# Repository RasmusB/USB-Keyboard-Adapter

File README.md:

# USB-Keyboard-Adapter

An ATmega32u4 based keyboard controller. This was designed for use with a Psion Series 5mx keyboard, but should work for other keyboards also.

* PCB contains KiCad files for the device itself
* Firmware/Psion-Keyboard-Firmware contains an Arduino sketch for the firmware
* Firmware/ScanTheMatrix is a sketch for scanning the matrix of a keyboard. This is only meant as a tool to map a keyboard with an unknown pinout.

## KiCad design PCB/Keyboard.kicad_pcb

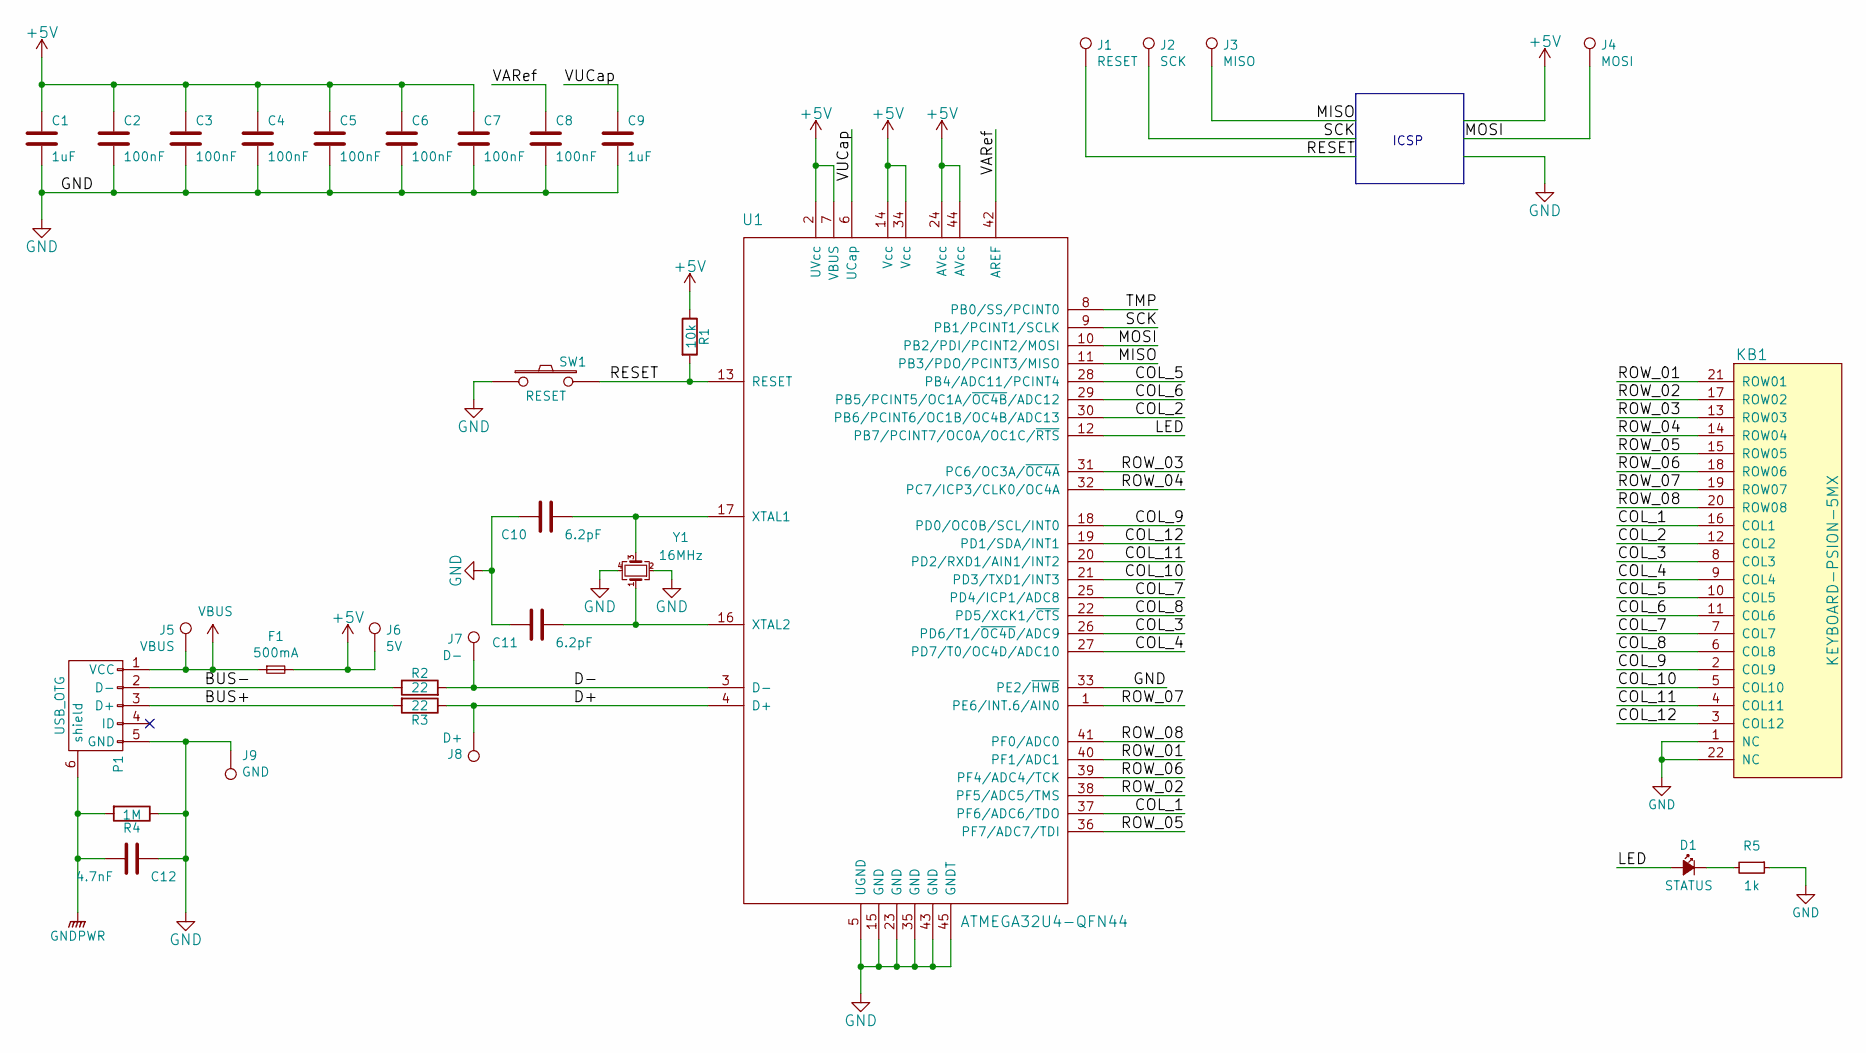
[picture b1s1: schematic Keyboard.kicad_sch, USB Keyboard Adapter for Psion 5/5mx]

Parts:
C1, C9: 1uF; C_0402_1005Metric; MPN CL05A105KA5NQNC; JLCPCB C52923
C2, C3, C4, C5, C6, C7, C8: 100nF; C_0402_1005Metric; MPN CL05B104KO5NNNC; JLCPCB C1525
C10, C11: 6.2pF; C_0402_1005Metric; MPN CC0402CRNPO9BN6R2; JLCPCB C325456
C12: 4.7nF; C_0402_1005Metric; MPN 0402B472K500NT; JLCPCB C1538
D1: STATUS; LED_0402_1005Metric; MPN XL-1005SURC; JLCPCB C965790
F1: 500mA; Fuse_0603_1608Metric; MPN 0603L100SLYR; JLCPCB C207017
J1: RESET; TESTPOINT-1mm-NO_TEXT
J2: SCK; TESTPOINT-1mm-NO_TEXT
J3: MISO; TESTPOINT-1mm-NO_TEXT
J4: MOSI; TESTPOINT-1mm-NO_TEXT
J5: VBUS; TESTPOINT-1mm-NO_TEXT
J6: 5V; TESTPOINT-1mm-NO_TEXT
J7: D-; TESTPOINT-1mm-NO_TEXT
J8: D+; TESTPOINT-1mm-NO_TEXT
J9: GND; TESTPOINT-1mm-NO_TEXT
KB1: KEYBOARD-PSION-5MX; FPC_22p-JUSHUO_AFC01-S22FCC-00; MPN AFC01-S22FCC-00; JLCPCB C262275
P1: USB_OTG; USB_Micro-B_Amphenol_10118194_Horizontal; MPN 10118194-0001LF; JLCPCB C132563
R1: 10k; R_0402_1005Metric; MPN 0402WGF1002TCE; JLCPCB C25744
R2, R3: 22; R_0402_1005Metric; MPN 0402WGF220JTCE; JLCPCB C25092
R4: 1M; R_0402_1005Metric; MPN 0402WGF1004TCE; JLCPCB C26083
R5: 1k; R_0402_1005Metric; MPN 0402WGF1001TCE; JLCPCB C11702
SW1: RESET; ALPS-SKRMAAE010; MPN SKRMAAE010; JLCPCB C115358
U1: ATMEGA32U4-QFN44; QFN-44-1EP_7x7mm_P0.5mm_EP5.2x5.2mm; MPN ATMEGA32U4-MU; JLCPCB C112161
Y1: 16MHz; Crystal_SMD_Abracon_ABM10-4Pin_2.5x2.0mm; MPN ABM10W-16.0000MHZ-8-D1X-T3; JLCPCB C1986789

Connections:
+5V: C1.1, C2.1, C3.1, C4.1, C5.1, C6.1, C7.1, F1.2, J6.1, R1.1, U1.2 (UVcc), U1.7 (VBUS), U1.14 (Vcc), U1.24 (AVcc), U1.34 (Vcc), U1.44 (AVcc)
/BUS+: P1.3 (D+), R3.2
/BUS-: P1.2 (D-), R2.1
/COL_1: KB1.16 (COL1), U1.37 (PF6/ADC6/TDO)
/COL_2: KB1.12 (COL2), U1.30 (PB6/PCINT6/OC1B/OC4B/ADC13)
/COL_3: KB1.8 (COL3), U1.26 (PD6/T1/~OC4D/ADC9)
/COL_4: KB1.9 (COL4), U1.27 (PD7/T0/OC4D/ADC10)
/COL_5: KB1.10 (COL5), U1.28 (PB4/ADC11/PCINT4)
/COL_6: KB1.11 (COL6), U1.29 (PB5/PCINT5/OC1A/~OC4B/ADC12)
/COL_7: KB1.7 (COL7), U1.25 (PD4/ICP1/ADC8)
/COL_8: KB1.6 (COL8), U1.22 (PD5/XCK1/~CTS)
/COL_9: KB1.2 (COL9), U1.18 (PD0/OC0B/SCL/INT0)
/COL_10: KB1.5 (COL10), U1.21 (PD3/TXD1/INT3)
/COL_11: KB1.4 (COL11), U1.20 (PD2/RXD1/AIN1/INT2)
/COL_12: KB1.3 (COL12), U1.19 (PD1/SDA/INT1)
/D+: J8.1, R3.1, U1.4 (D+)
/D-: J7.1, R2.2, U1.3 (D-)
/LED: D1.2 (A), U1.12 (PB7/PCINT7/OC0A/OC1C/~RTS)
/MISO: J3.1, U1.11 (PB3/PDO/PCINT3/MISO)
/MOSI: J4.1, U1.10 (PB2/PDI/PCINT2/MOSI)
/RESET: J1.1, R1.2, SW1.2, U1.13 (RESET)
/ROW_01: KB1.21 (ROW01), U1.40 (PF1/ADC1)
/ROW_02: KB1.17 (ROW02), U1.38 (PF5/ADC5/TMS)
/ROW_03: KB1.13 (ROW03), U1.31 (PC6/OC3A/~OC4A)
/ROW_04: KB1.14 (ROW04), U1.32 (PC7/ICP3/CLK0/OC4A)
/ROW_05: KB1.15 (ROW05), U1.36 (PF7/ADC7/TDI)
/ROW_06: KB1.18 (ROW06), U1.39 (PF4/ADC4/TCK)
/ROW_07: KB1.19 (ROW07), U1.1 (PE6/INT.6/AIN0)
/ROW_08: KB1.20 (ROW08), U1.41 (PF0/ADC0)
/SCK: J2.1, U1.9 (PB1/PCINT1/SCLK)
/TMP: U1.8 (PB0/SS/PCINT0)
/VARef: C8.1, U1.42 (AREF)
/VUCap: C9.1, U1.6 (UCap)
GND: C1.2, C2.2, C3.2, C4.2, C5.2, C6.2, C7.2, C8.2, C9.2, C10.2, C11.2, C12.1, J9.1, KB1.1 (NC), KB1.22 (NC), P1.5 (GND), R4.1, R5.1, SW1.1, U1.5 (UGND), U1.15 (GND), U1.23 (GND), U1.33 (PE2/~HWB), U1.35 (GND), U1.43 (GND), U1.45 (GNDT), Y1.2, Y1.4
GNDPWR: C12.2, P1.6 (shield), R4.2
unnamed: C10.1, U1.17 (XTAL1), Y1.3
unnamed: C11.1, U1.16 (XTAL2), Y1.1
unnamed: D1.1 (K), R5.2
VBUS: F1.1, J5.1, P1.1 (VCC)

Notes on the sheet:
ICSP

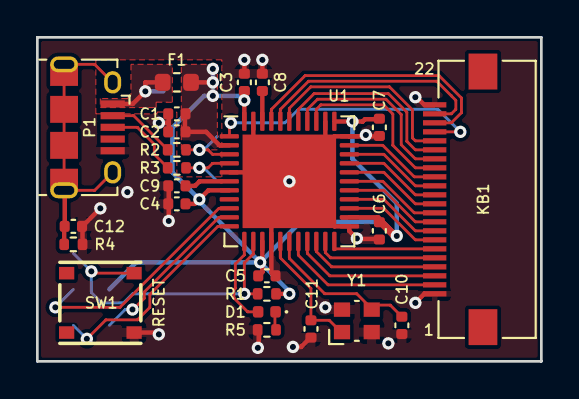
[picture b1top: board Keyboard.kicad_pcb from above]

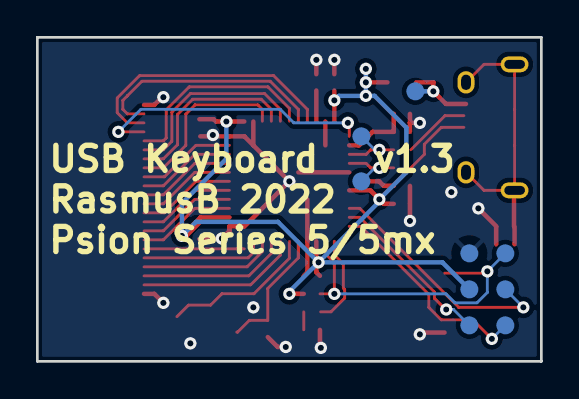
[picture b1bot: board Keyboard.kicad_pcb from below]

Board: 2 copper layers, 28.0 x 18.0 mm, 33 parts (9 on the bottom side), 38 nets.

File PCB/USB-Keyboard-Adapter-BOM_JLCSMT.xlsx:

Comment | Designator | Footprint | JLCPCB Part #（optional）
1µF | C1, C9 | C_0402 | C52923
100nF | C2, C3, C4, C5, C6, C7, C8 | C_0402 | C1525
6.2pF | C10, C11 | C_0402 | C325456
4.7nF | C12 | C_0402 | C1538
STATUS LED | D1 | LED_0402 | C965790
500mA Polyfuse | F1 | FUSE_0603 | C207017
22p FPC connector | KB1 | 22p FPC | C262275
USB Micro B | P1 | USB Micro B | C132563
10k | R1 | R_0402 | C25744
22R | R2, R3 | R_0402 | C25092
1M | R4 | R_0402 | C26083
1k | R5 | R_0402 | C11702
RESET BUTTON | SW1 | Switch | C115358
ATMEGA32U4-MU | U1 | QFN44 | C112161
16MHz | Y1 | 2.5x2.0mm 4pin | C1986789

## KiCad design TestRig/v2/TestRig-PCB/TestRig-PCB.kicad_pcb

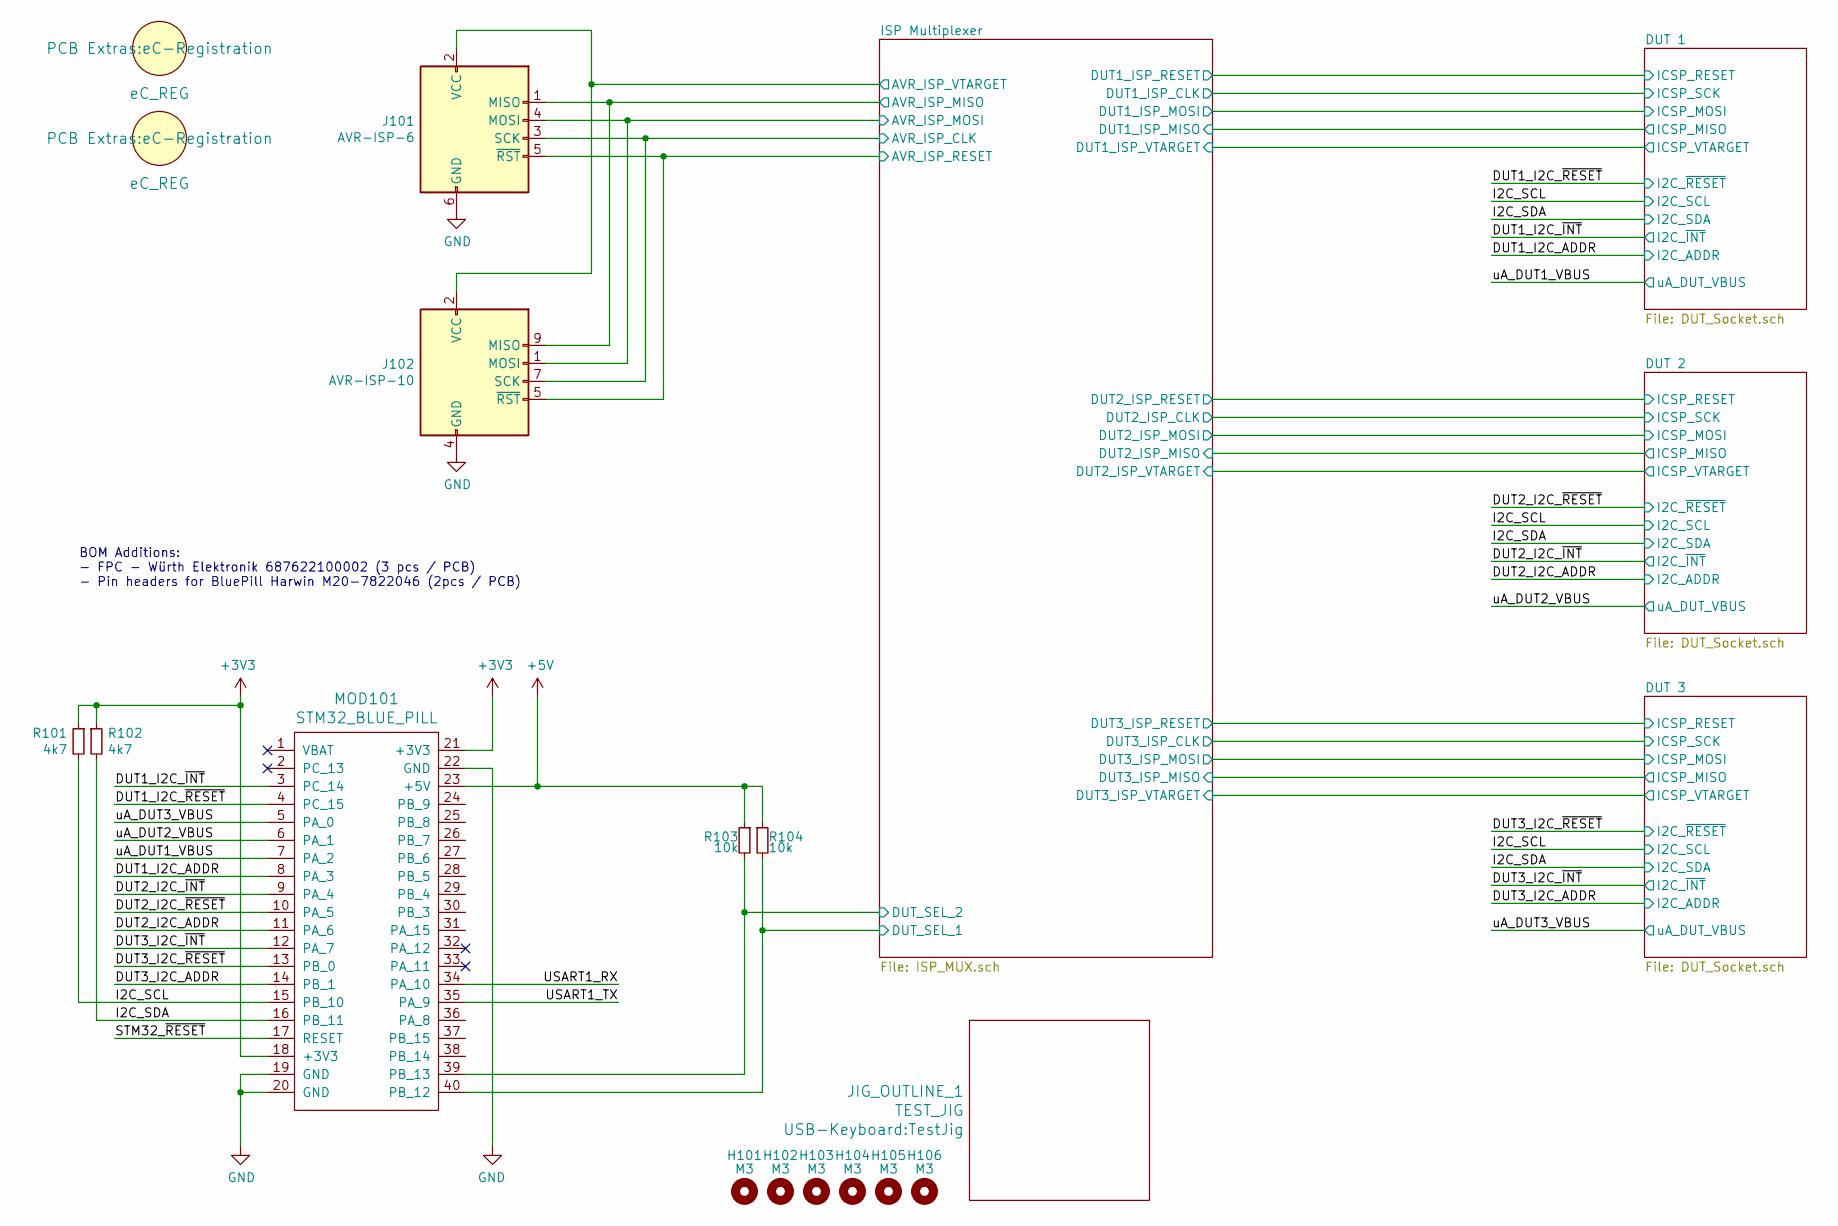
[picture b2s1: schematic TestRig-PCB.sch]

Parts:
H101, H102, H103, H104, H105, H106: M3; MountingHole_3.2mm_M3
J101: AVR-ISP-6; IDC-Header_2x03_P2.54mm_Vertical; MPN 87834-0619
J102: AVR-ISP-10; IDC-Header_2x05_P2.54mm_Vertical; MPN 70246-1001
JIG_OUTLINE_1: TEST_JIG; TestJig
MOD101: STM32_BLUE_PILL; STM32F103C8T6-ARM-BOARD
R101, R102: 4k7; R_0603_1608Metric; MPN CR0603-JW-472ELF
R103, R104: 10k; R_0603_1608Metric; MPN CR0603-JW-103ELF
REG101, REG102: eC_REG; eC-Registration

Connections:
+3V3: MOD101.18 (+3V3), MOD101.21 (+3V3), R101.1, R102.1; also elsewhere on the board
+5V: MOD101.23 (+5V), R103.1, R104.1; also elsewhere on the board
/DUT1_I2C_ADDR: MOD101.8 (PA_3); also elsewhere on the board
/DUT1_I2C_~INT: MOD101.3 (PC_14); also elsewhere on the board
/DUT1_I2C_~RESET: MOD101.4 (PC_15); also elsewhere on the board
/DUT2_I2C_ADDR: MOD101.11 (PA_6); also elsewhere on the board
/DUT2_I2C_~INT: MOD101.9 (PA_4); also elsewhere on the board
/DUT2_I2C_~RESET: MOD101.10 (PA_5); also elsewhere on the board
/DUT3_I2C_ADDR: MOD101.14 (PB_1); also elsewhere on the board
/DUT3_I2C_~INT: MOD101.12 (PA_7); also elsewhere on the board
/DUT3_I2C_~RESET: MOD101.13 (PB_0); also elsewhere on the board
/I2C_SCL: MOD101.15 (PB_10), R101.2; also elsewhere on the board
/I2C_SDA: MOD101.16 (PB_11), R102.2; also elsewhere on the board
/ISP Multiplexer/AVR_ISP_CLK: J101.3 (SCK), J102.7 (SCK); also elsewhere on the board
/ISP Multiplexer/AVR_ISP_MISO: J101.1 (MISO), J102.9 (MISO); also elsewhere on the board
/ISP Multiplexer/AVR_ISP_MOSI: J101.4 (MOSI), J102.1 (MOSI); also elsewhere on the board
/ISP Multiplexer/AVR_ISP_RESET: J101.5 (~RST), J102.5 (~RST); also elsewhere on the board
/ISP Multiplexer/AVR_ISP_VTARGET: J101.2 (VCC), J102.2 (VCC); also elsewhere on the board
/ISP Multiplexer/DUT_SEL_1: MOD101.40 (PB_12), R104.2; also elsewhere on the board
/ISP Multiplexer/DUT_SEL_2: MOD101.39 (PB_13), R103.2; also elsewhere on the board
/STM32_~RESET: MOD101.17 (RESET)
/USART1_RX: MOD101.34 (PA_10)
/USART1_TX: MOD101.35 (PA_9)
/uA_DUT1_VBUS: MOD101.7 (PA_2); also elsewhere on the board
/uA_DUT2_VBUS: MOD101.6 (PA_1); also elsewhere on the board
/uA_DUT3_VBUS: MOD101.5 (PA_0); also elsewhere on the board
GND: J101.6 (GND), J102.4 (GND), J102.6 (GND), J102.8 (GND), J102.10 (GND), MOD101.19 (GND), MOD101.20 (GND), MOD101.22 (GND); also elsewhere on the board

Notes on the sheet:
BOM Additions: - FPC - Würth Elektronik 687622100002 (3 pcs / PCB) - Pin headers for BluePill Harwin M20-7822046 (2pcs / PCB)

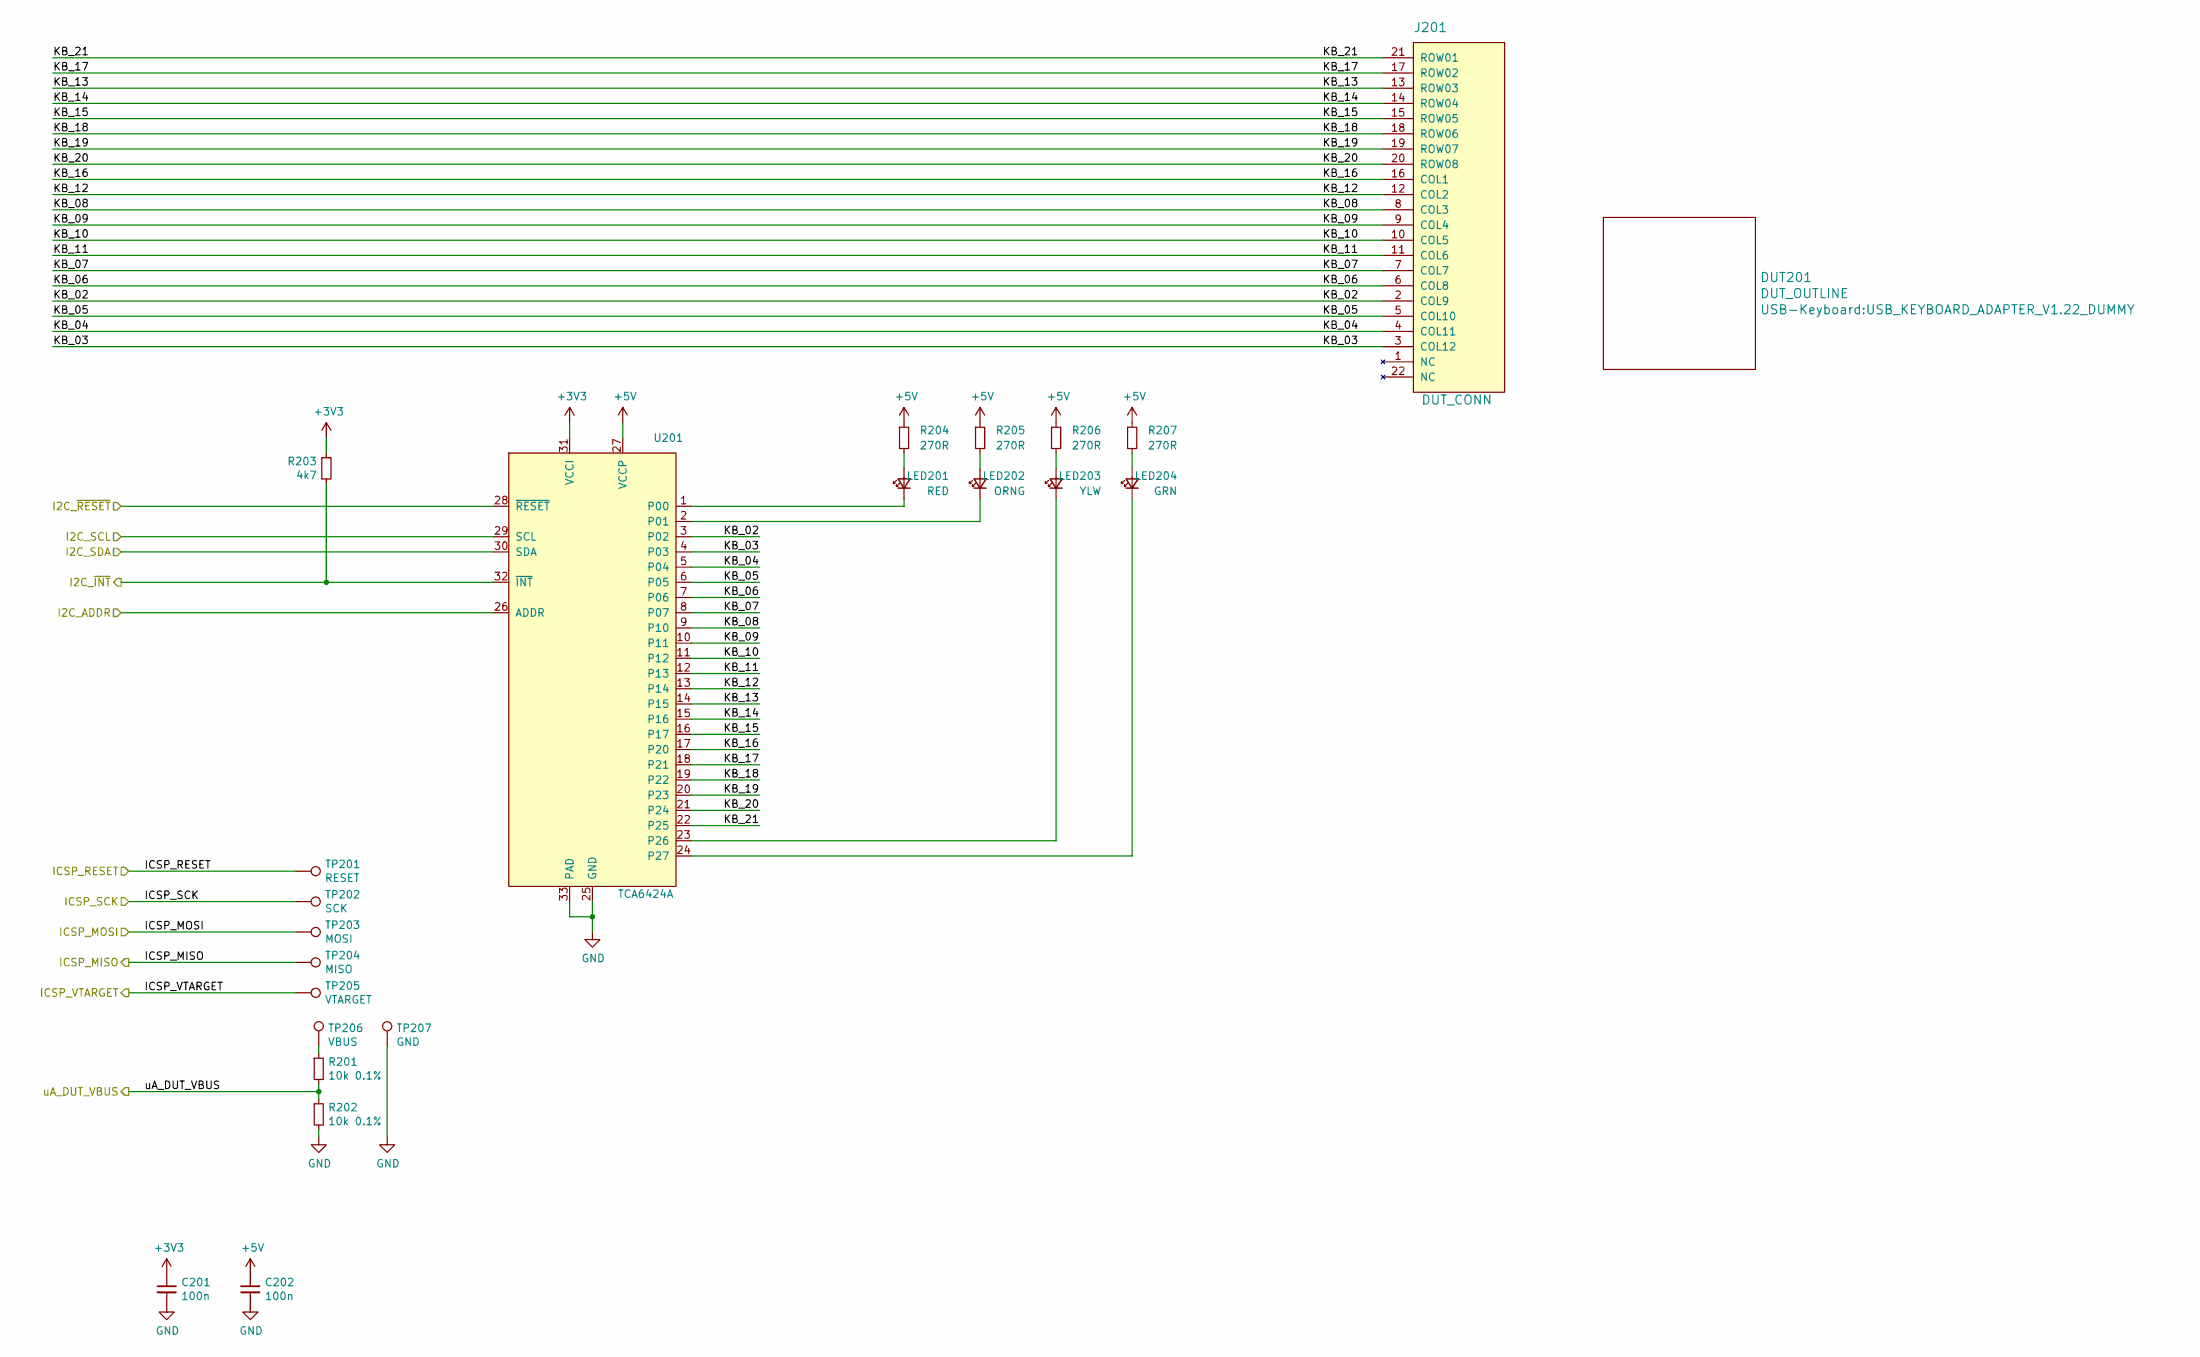
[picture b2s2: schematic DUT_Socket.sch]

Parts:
C201, C202: 100n; C_0603_1608Metric; MPN C0603C104Z3VACTU
DUT201: DUT_OUTLINE; USB_KEYBOARD_ADAPTER_V1.22_DUMMY
J201: DUT_CONN; Hirose_FH12-22S-0.5SH_1x22-1MP_P0.50mm_Horizontal; MPN FH12A-22S-0.5SH(55)
LED201: RED; LED_0603_1608Metric; MPN APT1608SRCPRV
LED202: ORNG; LED_0603_1608Metric; MPN APT1608SECK
LED203: YLW; LED_0603_1608Metric; MPN APT1608SYCK
LED204: GRN; LED_0603_1608Metric; MPN APT1608CGCK
R201, R202: 10k 0.1%; R_0603_1608Metric; MPN ERA-3AEB103V
R203: 4k7; R_0603_1608Metric; MPN CR0603-JW-472ELF
R204, R205, R206, R207: 270R; R_0603_1608Metric; MPN CRGCQ0603F270R
TP201: RESET; Pogo_P50_Bottom
TP202: SCK; Pogo_P50_Bottom
TP203: MOSI; Pogo_P50_Bottom
TP204: MISO; Pogo_P50_Bottom
TP205: VTARGET; Pogo_P50_Bottom
TP206: VBUS; Pogo_P50_Bottom
TP207: GND; Pogo_P50_Bottom
U201: TCA6424A; QFN-32-1EP_5x5mm_P0.5mm_EP3.1x3.1mm; MPN TCA6424ARGJR

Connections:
+3V3: C201.1, R203.1, U201.31 (VCCI); also elsewhere on the board
+5V: C202.1, R204.1, R205.1, R206.1, R207.1, U201.27 (VCCP); also elsewhere on the board
/DUT1_I2C_ADDR: U201.26 (ADDR); also elsewhere on the board
/DUT1_I2C_~INT: R203.2, U201.32 (~INT); also elsewhere on the board
/DUT1_I2C_~RESET: U201.28 (~RESET); also elsewhere on the board
/DUT 1/KB_02: J201.2 (COL9), U201.3 (P02)
/DUT 1/KB_03: J201.3 (COL12), U201.4 (P03)
/DUT 1/KB_04: J201.4 (COL11), U201.5 (P04)
/DUT 1/KB_05: J201.5 (COL10), U201.6 (P05)
/DUT 1/KB_06: J201.6 (COL8), U201.7 (P06)
/DUT 1/KB_07: J201.7 (COL7), U201.8 (P07)
/DUT 1/KB_08: J201.8 (COL3), U201.9 (P10)
/DUT 1/KB_09: J201.9 (COL4), U201.10 (P11)
/DUT 1/KB_10: J201.10 (COL5), U201.11 (P12)
/DUT 1/KB_11: J201.11 (COL6), U201.12 (P13)
/DUT 1/KB_12: J201.12 (COL2), U201.13 (P14)
/DUT 1/KB_13: J201.13 (ROW03), U201.14 (P15)
/DUT 1/KB_14: J201.14 (ROW04), U201.15 (P16)
/DUT 1/KB_15: J201.15 (ROW05), U201.16 (P17)
/DUT 1/KB_16: J201.16 (COL1), U201.17 (P20)
/DUT 1/KB_17: J201.17 (ROW02), U201.18 (P21)
/DUT 1/KB_18: J201.18 (ROW06), U201.19 (P22)
/DUT 1/KB_19: J201.19 (ROW07), U201.20 (P23)
/DUT 1/KB_20: J201.20 (ROW08), U201.21 (P24)
/DUT 1/KB_21: J201.21 (ROW01), U201.22 (P25)
/I2C_SCL: U201.29 (SCL); also elsewhere on the board
/I2C_SDA: U201.30 (SDA); also elsewhere on the board
/ISP Multiplexer/DUT1_ISP_CLK: TP202.1; also elsewhere on the board
/ISP Multiplexer/DUT1_ISP_MISO: TP204.1; also elsewhere on the board
/ISP Multiplexer/DUT1_ISP_MOSI: TP203.1; also elsewhere on the board
/ISP Multiplexer/DUT1_ISP_RESET: TP201.1; also elsewhere on the board
/ISP Multiplexer/DUT1_ISP_VTARGET: TP205.1; also elsewhere on the board
/uA_DUT1_VBUS: R201.2, R202.1; also elsewhere on the board
GND: C201.2, C202.2, R202.2, TP207.1, U201.25 (GND), U201.33 (PAD); also elsewhere on the board
unnamed: LED201.1 (K), U201.1 (P00)
unnamed: LED201.2 (A), R204.2
unnamed: LED202.1 (K), U201.2 (P01)
unnamed: LED202.2 (A), R205.2
unnamed: LED203.1 (K), U201.23 (P26)
unnamed: LED203.2 (A), R206.2
unnamed: LED204.1 (K), U201.24 (P27)
unnamed: LED204.2 (A), R207.2
unnamed: R201.1, TP206.1

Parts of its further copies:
C401, C402, C501, C502: 100n; C_0603_1608Metric; MPN C0603C104Z3VACTU
DUT401, DUT501: DUT_OUTLINE; USB_KEYBOARD_ADAPTER_V1.22_DUMMY
J401, J501: DUT_CONN; Hirose_FH12-22S-0.5SH_1x22-1MP_P0.50mm_Horizontal; MPN FH12A-22S-0.5SH(55)
LED401, LED501: RED; LED_0603_1608Metric; MPN APT1608SRCPRV
LED402, LED502: ORNG; LED_0603_1608Metric; MPN APT1608SECK
LED403, LED503: YLW; LED_0603_1608Metric; MPN APT1608SYCK
LED404, LED504: GRN; LED_0603_1608Metric; MPN APT1608CGCK
R403, R503: 4k7; R_0603_1608Metric; MPN CR0603-JW-472ELF
R404, R405, R406, R407, R504, R505, R506, R507: 270R; R_0603_1608Metric; MPN CRGCQ0603F270R
TP401, TP501: RESET; Pogo_P50_Bottom
TP402, TP502: SCK; Pogo_P50_Bottom
TP403, TP503: MOSI; Pogo_P50_Bottom
TP404, TP504: MISO; Pogo_P50_Bottom
TP405, TP505: VTARGET; Pogo_P50_Bottom
TP406, TP506: VBUS; Pogo_P50_Bottom
TP407, TP507: GND; Pogo_P50_Bottom
U401, U501: TCA6424A; QFN-32-1EP_5x5mm_P0.5mm_EP3.1x3.1mm; MPN TCA6424ARGJR

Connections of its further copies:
+3V3: C401.1, C501.1, R403.1, R503.1, U401.31 (VCCI), U501.31 (VCCI); also elsewhere on the board
+5V: C402.1, C502.1, R404.1, R405.1, R406.1, R407.1, R504.1, R505.1, R506.1, R507.1, U401.27 (VCCP), U501.27 (VCCP); also elsewhere on the board
/DUT2_I2C_ADDR: U401.26 (ADDR); also elsewhere on the board
/DUT2_I2C_~INT: R403.2, U401.32 (~INT); also elsewhere on the board
/DUT2_I2C_~RESET: U401.28 (~RESET); also elsewhere on the board
/DUT3_I2C_ADDR: U501.26 (ADDR); also elsewhere on the board
/DUT3_I2C_~INT: R503.2, U501.32 (~INT); also elsewhere on the board
/DUT3_I2C_~RESET: U501.28 (~RESET); also elsewhere on the board
/DUT 2/KB_02: J401.2 (COL9), U401.3 (P02)
/DUT 2/KB_03: J401.3 (COL12), U401.4 (P03)
/DUT 2/KB_04: J401.4 (COL11), U401.5 (P04)
/DUT 2/KB_05: J401.5 (COL10), U401.6 (P05)
/DUT 2/KB_06: J401.6 (COL8), U401.7 (P06)
/DUT 2/KB_07: J401.7 (COL7), U401.8 (P07)
/DUT 2/KB_08: J401.8 (COL3), U401.9 (P10)
/DUT 2/KB_09: J401.9 (COL4), U401.10 (P11)
/DUT 2/KB_10: J401.10 (COL5), U401.11 (P12)
/DUT 2/KB_11: J401.11 (COL6), U401.12 (P13)
/DUT 2/KB_12: J401.12 (COL2), U401.13 (P14)
/DUT 2/KB_13: J401.13 (ROW03), U401.14 (P15)
/DUT 2/KB_14: J401.14 (ROW04), U401.15 (P16)
/DUT 2/KB_15: J401.15 (ROW05), U401.16 (P17)
/DUT 2/KB_16: J401.16 (COL1), U401.17 (P20)
/DUT 2/KB_17: J401.17 (ROW02), U401.18 (P21)
/DUT 2/KB_18: J401.18 (ROW06), U401.19 (P22)
/DUT 2/KB_19: J401.19 (ROW07), U401.20 (P23)
/DUT 2/KB_20: J401.20 (ROW08), U401.21 (P24)
/DUT 2/KB_21: J401.21 (ROW01), U401.22 (P25)
/DUT 3/KB_02: J501.2 (COL9), U501.3 (P02)
/DUT 3/KB_03: J501.3 (COL12), U501.4 (P03)
/DUT 3/KB_04: J501.4 (COL11), U501.5 (P04)
/DUT 3/KB_05: J501.5 (COL10), U501.6 (P05)
/DUT 3/KB_06: J501.6 (COL8), U501.7 (P06)
/DUT 3/KB_07: J501.7 (COL7), U501.8 (P07)
/DUT 3/KB_08: J501.8 (COL3), U501.9 (P10)
/DUT 3/KB_09: J501.9 (COL4), U501.10 (P11)
/DUT 3/KB_10: J501.10 (COL5), U501.11 (P12)
/DUT 3/KB_11: J501.11 (COL6), U501.12 (P13)
/DUT 3/KB_12: J501.12 (COL2), U501.13 (P14)
/DUT 3/KB_13: J501.13 (ROW03), U501.14 (P15)
/DUT 3/KB_14: J501.14 (ROW04), U501.15 (P16)
/DUT 3/KB_15: J501.15 (ROW05), U501.16 (P17)
/DUT 3/KB_16: J501.16 (COL1), U501.17 (P20)
/DUT 3/KB_17: J501.17 (ROW02), U501.18 (P21)
/DUT 3/KB_18: J501.18 (ROW06), U501.19 (P22)
/DUT 3/KB_19: J501.19 (ROW07), U501.20 (P23)
/DUT 3/KB_20: J501.20 (ROW08), U501.21 (P24)
/DUT 3/KB_21: J501.21 (ROW01), U501.22 (P25)
/I2C_SCL: U401.29 (SCL), U501.29 (SCL); also elsewhere on the board
/I2C_SDA: U401.30 (SDA), U501.30 (SDA); also elsewhere on the board
/ISP Multiplexer/DUT2_ISP_CLK: TP402.1; also elsewhere on the board
/ISP Multiplexer/DUT2_ISP_MISO: TP404.1; also elsewhere on the board
/ISP Multiplexer/DUT2_ISP_MOSI: TP403.1; also elsewhere on the board
/ISP Multiplexer/DUT2_ISP_RESET: TP401.1; also elsewhere on the board
/ISP Multiplexer/DUT2_ISP_VTARGET: TP405.1; also elsewhere on the board
/ISP Multiplexer/DUT3_ISP_CLK: TP502.1; also elsewhere on the board
/ISP Multiplexer/DUT3_ISP_MISO: TP504.1; also elsewhere on the board
/ISP Multiplexer/DUT3_ISP_MOSI: TP503.1; also elsewhere on the board
/ISP Multiplexer/DUT3_ISP_RESET: TP501.1; also elsewhere on the board
/ISP Multiplexer/DUT3_ISP_VTARGET: TP505.1; also elsewhere on the board
GND: C401.2, C402.2, C501.2, C502.2, TP407.1, TP507.1, U401.25 (GND), U401.33 (PAD), U501.25 (GND), U501.33 (PAD); also elsewhere on the board
unnamed: LED401.1 (K), U401.1 (P00)
unnamed: LED401.2 (A), R404.2
unnamed: LED402.1 (K), U401.2 (P01)
unnamed: LED402.2 (A), R405.2
unnamed: LED403.1 (K), U401.23 (P26)
unnamed: LED403.2 (A), R406.2
unnamed: LED404.1 (K), U401.24 (P27)
unnamed: LED404.2 (A), R407.2
unnamed: LED501.1 (K), U501.1 (P00)
unnamed: LED501.2 (A), R504.2
unnamed: LED502.1 (K), U501.2 (P01)
unnamed: LED502.2 (A), R505.2
unnamed: LED503.1 (K), U501.23 (P26)
unnamed: LED503.2 (A), R506.2
unnamed: LED504.1 (K), U501.24 (P27)
unnamed: LED504.2 (A), R507.2
unnamed 149: TP406.1; also elsewhere on the board
unnamed 150: TP506.1; also elsewhere on the board

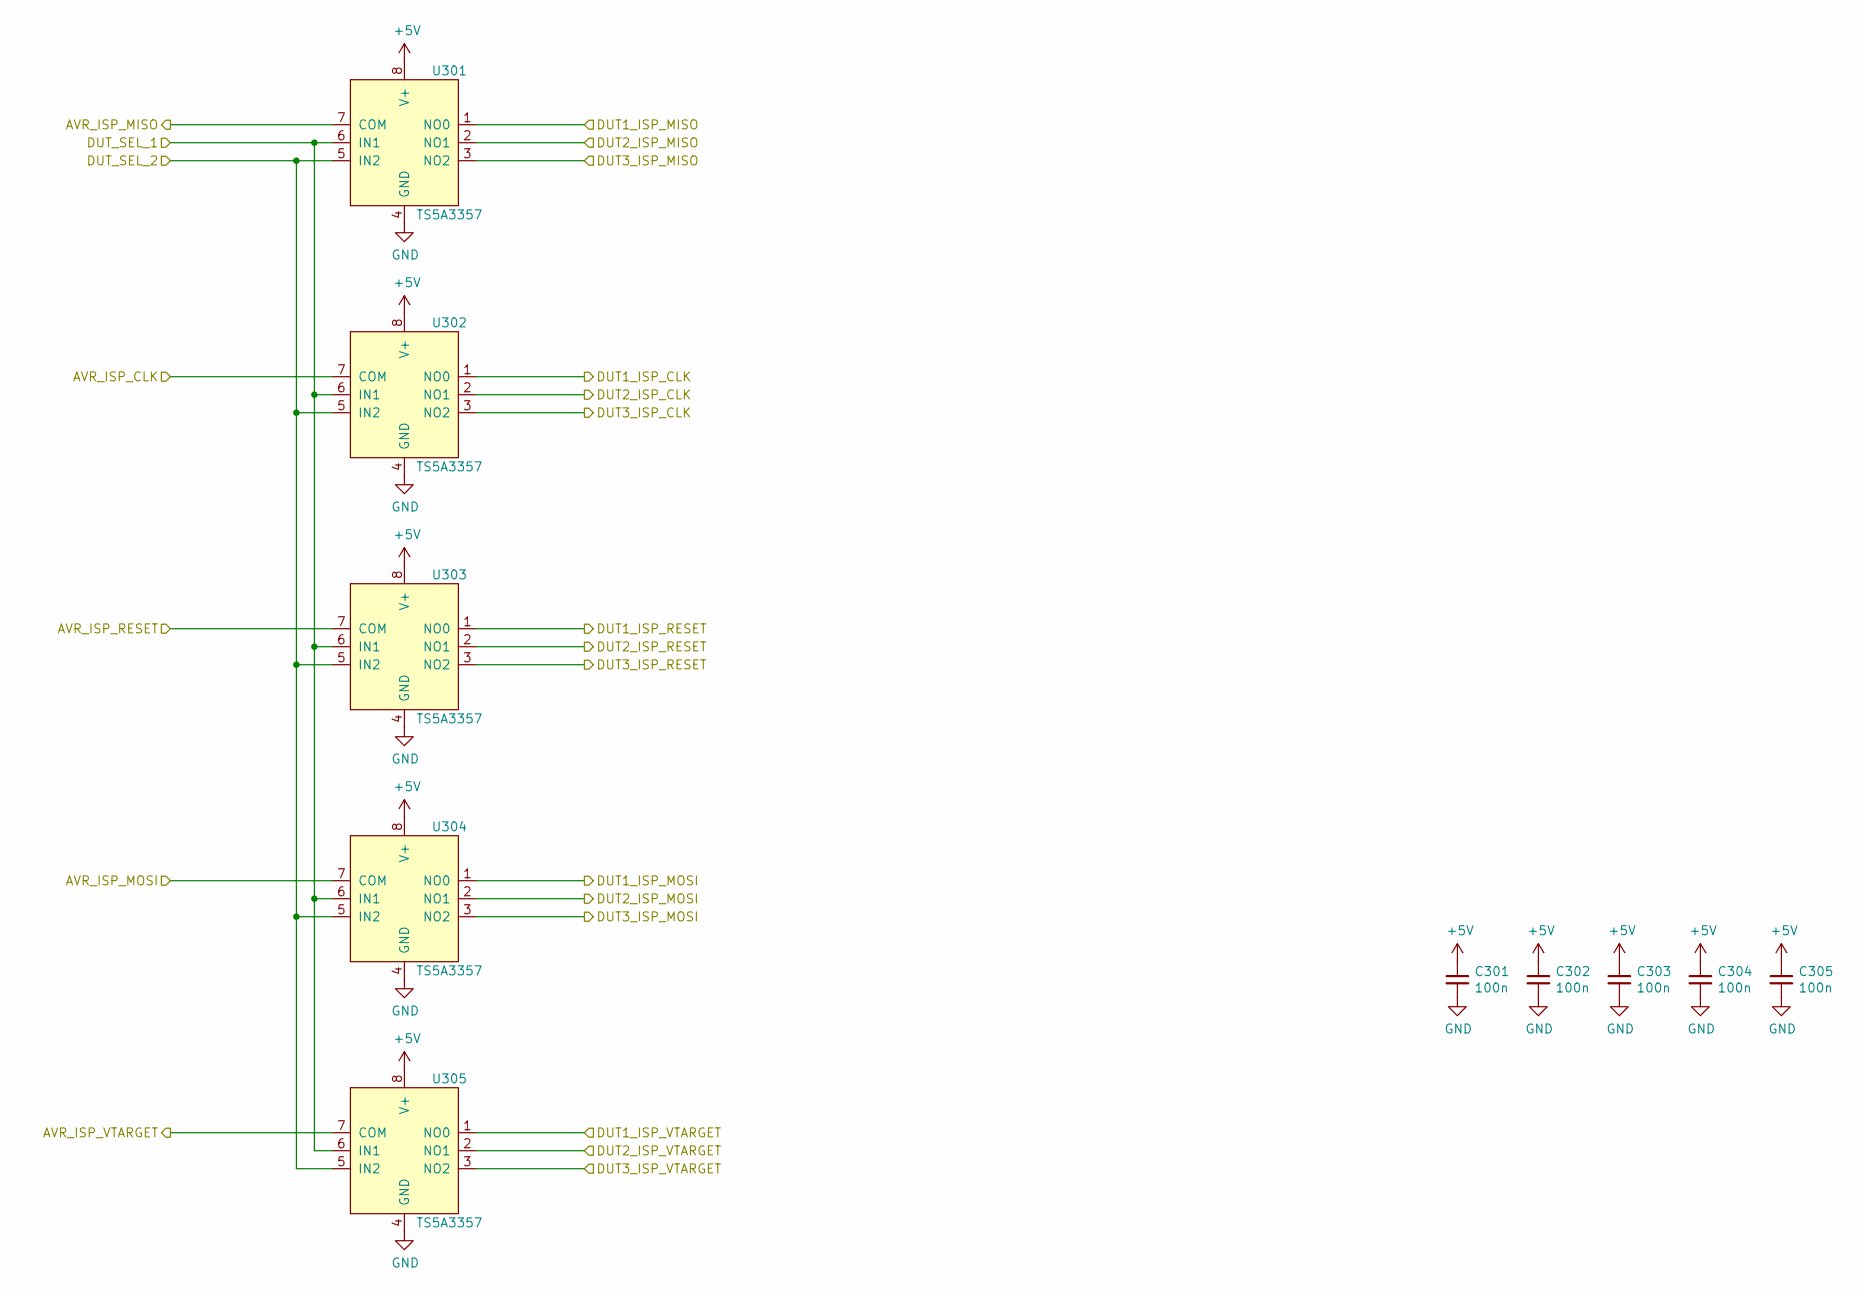
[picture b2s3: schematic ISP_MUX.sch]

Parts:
C301, C302, C303, C304, C305: 100n; C_0603_1608Metric; MPN C0603C104Z3VACTU
U301, U302, U303, U304, U305: TS5A3357; VSSOP-8_2.3x2mm_P0.5mm; MPN TS5A3357DCUR

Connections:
+5V: C301.1, C302.1, C303.1, C304.1, C305.1, U301.8 (V+), U302.8 (V+), U303.8 (V+), U304.8 (V+), U305.8 (V+); also elsewhere on the board
/ISP Multiplexer/AVR_ISP_CLK: U302.7 (COM); also elsewhere on the board
/ISP Multiplexer/AVR_ISP_MISO: U301.7 (COM); also elsewhere on the board
/ISP Multiplexer/AVR_ISP_MOSI: U304.7 (COM); also elsewhere on the board
/ISP Multiplexer/AVR_ISP_RESET: U303.7 (COM); also elsewhere on the board
/ISP Multiplexer/AVR_ISP_VTARGET: U305.7 (COM); also elsewhere on the board
/ISP Multiplexer/DUT1_ISP_CLK: U302.1 (NO0); also elsewhere on the board
/ISP Multiplexer/DUT1_ISP_MISO: U301.1 (NO0); also elsewhere on the board
/ISP Multiplexer/DUT1_ISP_MOSI: U304.1 (NO0); also elsewhere on the board
/ISP Multiplexer/DUT1_ISP_RESET: U303.1 (NO0); also elsewhere on the board
/ISP Multiplexer/DUT1_ISP_VTARGET: U305.1 (NO0); also elsewhere on the board
/ISP Multiplexer/DUT2_ISP_CLK: U302.2 (NO1); also elsewhere on the board
/ISP Multiplexer/DUT2_ISP_MISO: U301.2 (NO1); also elsewhere on the board
/ISP Multiplexer/DUT2_ISP_MOSI: U304.2 (NO1); also elsewhere on the board
/ISP Multiplexer/DUT2_ISP_RESET: U303.2 (NO1); also elsewhere on the board
/ISP Multiplexer/DUT2_ISP_VTARGET: U305.2 (NO1); also elsewhere on the board
/ISP Multiplexer/DUT3_ISP_CLK: U302.3 (NO2); also elsewhere on the board
/ISP Multiplexer/DUT3_ISP_MISO: U301.3 (NO2); also elsewhere on the board
/ISP Multiplexer/DUT3_ISP_MOSI: U304.3 (NO2); also elsewhere on the board
/ISP Multiplexer/DUT3_ISP_RESET: U303.3 (NO2); also elsewhere on the board
/ISP Multiplexer/DUT3_ISP_VTARGET: U305.3 (NO2); also elsewhere on the board
/ISP Multiplexer/DUT_SEL_1: U301.6 (IN1), U302.6 (IN1), U303.6 (IN1), U304.6 (IN1), U305.6 (IN1); also elsewhere on the board
/ISP Multiplexer/DUT_SEL_2: U301.5 (IN2), U302.5 (IN2), U303.5 (IN2), U304.5 (IN2), U305.5 (IN2); also elsewhere on the board
GND: C301.2, C302.2, C303.2, C304.2, C305.2, U301.4 (GND), U302.4 (GND), U303.4 (GND), U304.4 (GND), U305.4 (GND); also elsewhere on the board

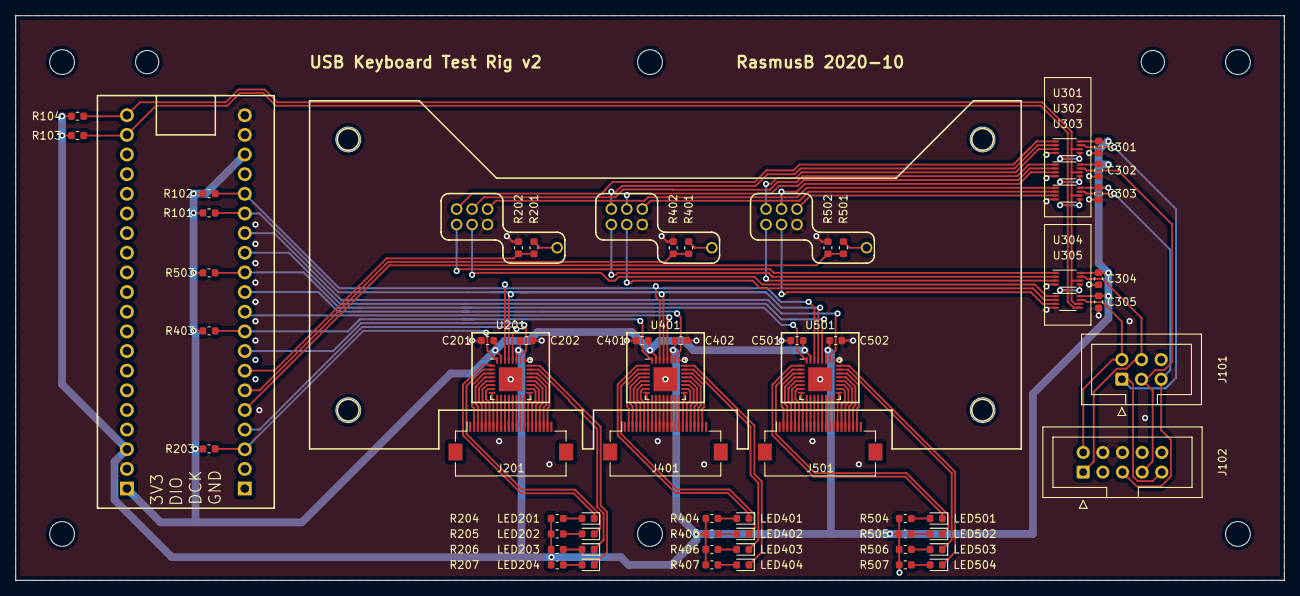
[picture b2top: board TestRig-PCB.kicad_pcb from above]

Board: 2 copper layers, 164.0 x 73.0 mm, 95 parts (0 on the bottom side), 126 nets.

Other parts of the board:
R401, R402, R501, R502: 10k 1%; R_0603_1608Metric

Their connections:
/uA_DUT2_VBUS: R401.2, R402.1; also elsewhere on the board
/uA_DUT3_VBUS: R501.2, R502.1; also elsewhere on the board
GND: R402.2, R502.2; also elsewhere on the board
unnamed 149: R401.1; also elsewhere on the board
unnamed 150: R501.1; also elsewhere on the board
